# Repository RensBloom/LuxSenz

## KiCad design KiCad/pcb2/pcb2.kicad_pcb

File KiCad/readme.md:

This folder contains the designs of the PCB designs made for the LuxSenz project. This includes a PCB design for the LuxSenz receiver, and an expansion board for a Nucleo-64 board that is used in the LuxSenz demo transmitter. The files in all folders can be opened in [KiCad](http://kicad-pcb.org) software.

The following folders exist:
- `pcb2`: the PCB design of the LuxSenz receiver
- `pcb3`: the PCB design of the expansion board for Nucleo-64, used in the LuxSenz demo transmitter

Each of these folders contain the following files and subfolders (as well as some other files):
- `library`: library files of components that were not yet available in the default libraries. Most of these libraries have been merged later on into the default KiCad libraries
- `gerber` or `gerber-rev*`: the generated gerber files that were sent to fabricating companies (for revision * of the board)
- `*.pro`: the KiCad project file. This one is the file that must be opened to view the designs in KiCad.

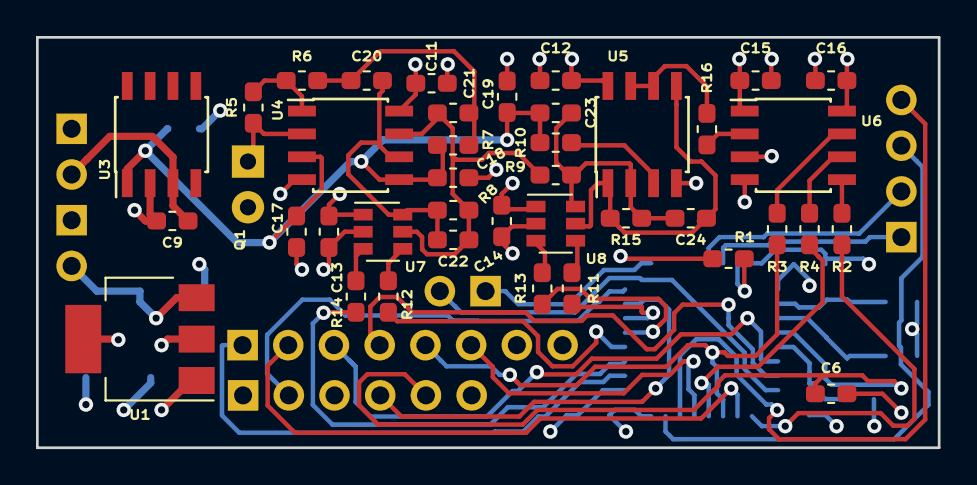
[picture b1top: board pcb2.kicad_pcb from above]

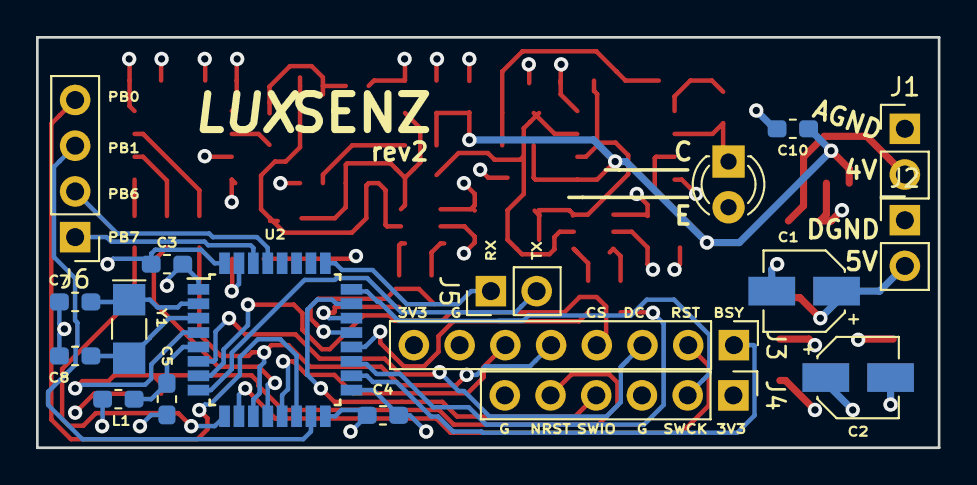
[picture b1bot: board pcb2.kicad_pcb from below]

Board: 4 copper layers, 50.1 x 22.8 mm, 57 parts (18 on the bottom side), 48 nets.

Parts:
C1, C2: 10u; CP_Elec_4x5.4
C3, C4, C5, C6, C13, C14, C17, C18, C19: 100n; C_0603_1608Metric_Pad1.05x0.95mm_HandSolder
C7, C8: ?pF; C_0603_1608Metric_Pad1.05x0.95mm_HandSolder
C9: 10u; C_0603_1608Metric_Pad1.05x0.95mm_HandSolder
C10, C11, C12, C15, C16, C20, C21: 1u; C_0603_1608Metric_Pad1.05x0.95mm_HandSolder
C22, C23, C24: option; C_0603_1608Metric_Pad1.05x0.95mm_HandSolder
J1, J2: Conn_01x02; PinHeader_1x02_P2.54mm_Vertical
J3: E-INK; PinHeader_1x08_P2.54mm_Vertical
J4: Conn_01x06_Male; PinHeader_1x06_P2.54mm_Vertical
J5: Conn_01x02_Male; PinHeader_1x02_P2.54mm_Vertical
J6: Conn_01x04_Male; PinHeader_1x04_P2.54mm_Vertical
L1: BEAD; L_0603_1608Metric_Pad1.05x0.95mm_HandSolder
Q1: TEPT4400; LED_D3.0mm_Clear
R1: 10k; R_0603_1608Metric_Pad1.05x0.95mm_HandSolder
R2, R3, R4, R11, R12, R13, R14: 1k5; R_0603_1608Metric_Pad1.05x0.95mm_HandSolder
R5: 68k indoor; R_0603_1608Metric_Pad1.05x0.95mm_HandSolder
R6: 300; R_0603_1608Metric_Pad1.05x0.95mm_HandSolder
R7: 68; R_0603_1608Metric_Pad1.05x0.95mm_HandSolder
R8, R15: 1k-100k; R_0603_1608Metric_Pad1.05x0.95mm_HandSolder
R9: 100-3k; R_0603_1608Metric_Pad1.05x0.95mm_HandSolder
R10: 0; R_0603_1608Metric_Pad1.05x0.95mm_HandSolder
R16: 2k2; R_0603_1608Metric_Pad1.05x0.95mm_HandSolder
U1: AMS1117-3.3; SOT-223-3_TabPin2
U2: STM32L031K6Tx; LQFP-32_7x7mm_P0.8mm
U3: TLE2425xD; SOIC-8_3.9x4.9mm_P1.27mm
U4, U5: OPA2325; SOIC-8_3.9x4.9mm_P1.27mm
U6: MCP3201; SOIC-8_3.9x4.9mm_P1.27mm
U7, U8: MCP4012-x503CH; SOT-23-6
Y1: 32.768k; Crystal_SMD_G8-2Pin_3.2x1.5mm_HandSoldering

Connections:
+2V5: C10.1, C17.1, C18.2, C19.1, C23.2, R7.1, R10.2, U3.1, U4.3, U4.5
+3V3: C2.1, C3.2, C4.2, J3.8, J4.1, L1.2, U1.2, U2.1, U2.17
+4V: C9.1, C11.1, C12.1, C13.1, C14.1, C15.1, C16.2, J1.2, U3.3, U4.8, U5.8, U6.1, U6.8, U7.1, U8.1
+5V: C1.1, J2.2, U1.3
/ADC_CLK: J3.5, R3.2, U2.11
/ADC_CS: R2.2, U2.9
/ADC_DIN: R4.2, U2.12
/EINK_BUSY: J3.1, U2.18
/EINK_CS: J3.4, U2.7
/EINK_DC: J3.3, U2.6
/EINK_DOUT: J3.6, U2.13
/EINK_RST: J3.2, U2.10
/MCU_CLK: R3.1, U6.7
/MCU_CS: R2.1, U6.5
/MCU_DOUT: R4.1, U6.6
/NRST: C6.1, J4.5, U2.4
/PB0: J6.4, U2.14
/PB1: J6.3, U2.15
/PB6: J6.2, U2.29
/PB7: J6.1, U2.30
/SWCLK: J4.2, U2.24
/SWDIO: J4.4, U2.23
/U7U~D: R14.1, U2.19
/U7~CS: R12.1, U2.20
/U8U~D: R13.1, U2.21
/U8~CS: R11.1, U2.22
/VCPRX: J5.1, U2.25
/VCPTX: J5.2, U2.8
GNDA: C9.2, C10.2, C11.2, C12.2, C13.2, C14.2, C15.2, C16.1, C17.2, C18.1, C19.2, J1.1, Q1.2, U3.2, U4.4, U5.4, U6.3, U6.4, U7.2, U8.2
GNDD: C1.2, C2.2, C3.1, C4.1, C5.1, C6.2, C7.2, C8.2, J2.1, J3.7, J4.3, J4.6, R1.1, U1.1, U2.16, U2.32
unnamed: C5.2, L1.1, U2.5
unnamed: C7.1, U2.2, Y1.1
unnamed: C8.1, U2.3, Y1.2
unnamed: C20.1, C22.2, R8.2, U4.6, U7.6
unnamed: C20.2, C21.2, R6.1, R7.2
unnamed: C21.1, C22.1, R8.1, R9.2, U4.7, U7.5
unnamed: C23.1, C24.2, R9.1, R15.2, U5.2, U8.6
unnamed: C24.1, R15.1, U5.1, U5.5, U8.5
unnamed: Q1.1, R5.1, U4.2
unnamed: R1.2, U2.31
unnamed: R5.2, R6.2, U4.1
unnamed: R10.1, U5.3
unnamed: R11.2, U8.4
unnamed: R12.2, U7.4
unnamed: R13.2, U8.3
unnamed: R14.2, U7.3
unnamed: R16.1, U6.2
unnamed: R16.2, U5.6, U5.7

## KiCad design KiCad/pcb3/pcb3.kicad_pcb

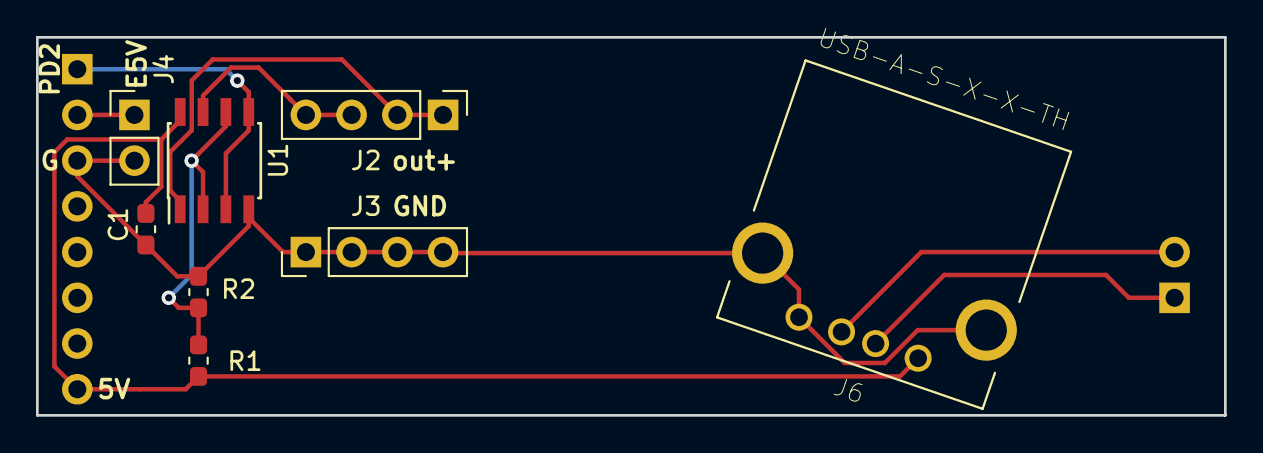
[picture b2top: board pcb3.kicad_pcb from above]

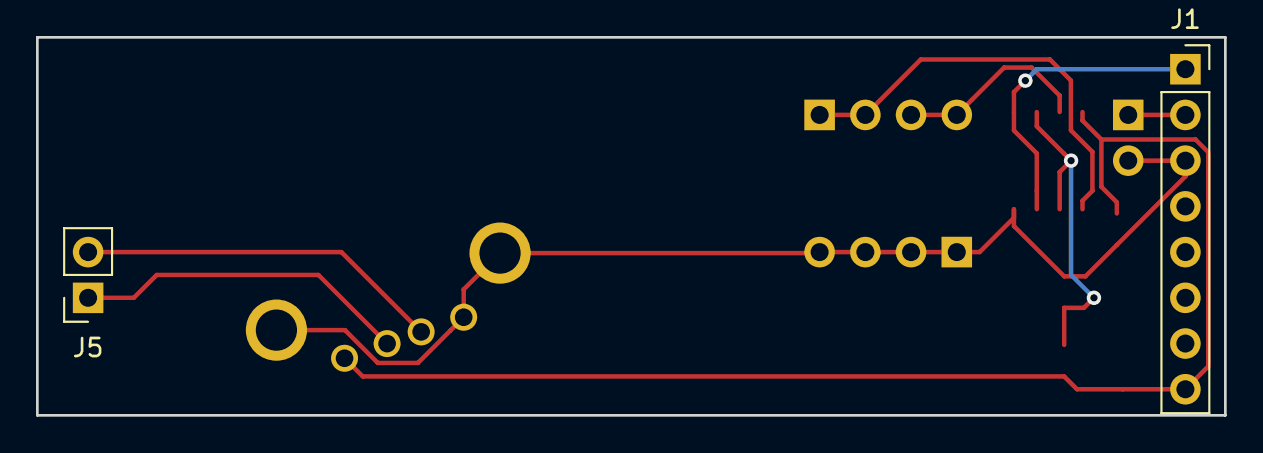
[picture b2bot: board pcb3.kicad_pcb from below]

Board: 2 copper layers, 66.0 x 21.0 mm, 10 parts (2 on the bottom side), 9 nets.

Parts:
C1: 1u; C_0603_1608Metric_Pad1.05x0.95mm_HandSolder
J1: Conn_01x08_Female; PinSocket_1x08_P2.54mm_Vertical
J2, J3: Conn_01x04_Female; PinHeader_1x04_P2.54mm_Vertical
J4: Conn_01x02_Male; PinHeader_1x02_P2.54mm_Vertical
J5: Conn_01x02_Female; PinSocket_1x02_P2.54mm_Vertical
J6: USB-A-S-X-X-TH
R1, R2: 1k5; R_0603_1608Metric_Pad1.05x0.95mm_HandSolder
U1: OPA2325; SOIC-8_3.9x4.9mm_P1.27mm

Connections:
/5V: C1.1, J1.8, J6.1, R1.2, U1.8
/G: C1.2, J1.3, J3.1, J3.2, J3.3, J3.4, J4.2, J6.4, J6.5, J6.6, R2.2, U1.4
/PD2: J1.1, U1.3, U1.5
/geel: J5.2, J6.3
/wit: J5.1, J6.2
unnamed: J1.2, J4.1
unnamed: J2.1, J2.2, U1.1
unnamed: J2.3, J2.4, U1.7
unnamed: R1.1, R2.1, U1.2, U1.6

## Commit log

2020-05-22 Commit my work
